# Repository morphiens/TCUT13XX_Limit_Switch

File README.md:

# TCUT13XX_Limit_Switch
Micro-limit-switch Using TCUT1300X01 Series  In this limit switch 2 Emitter are there for Redundancy , if some how on e get damage we have other one for use as backup

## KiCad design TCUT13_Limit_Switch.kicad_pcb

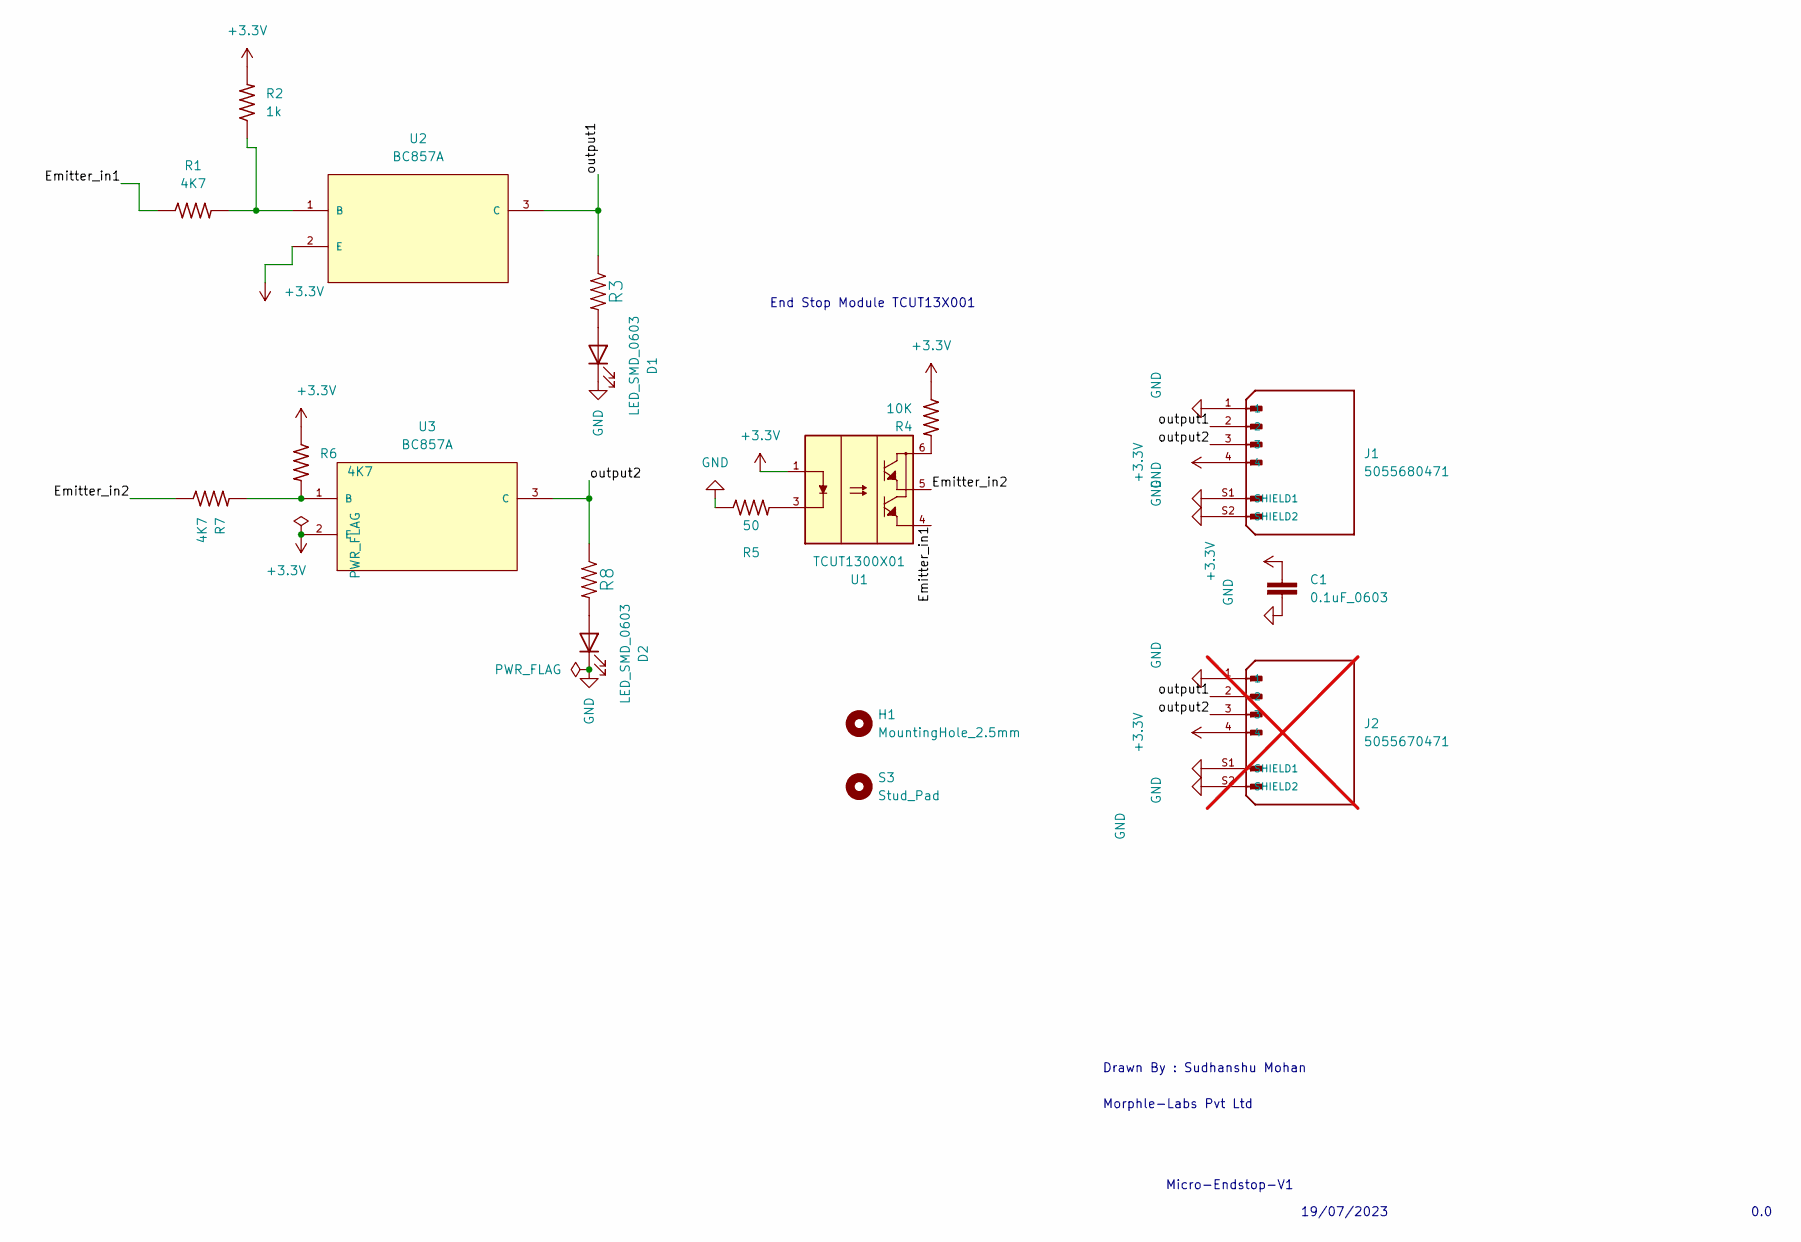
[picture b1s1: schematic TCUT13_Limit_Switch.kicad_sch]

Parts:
C1: 0.1uF_0603; Cap_0603_1608Metric
D1, D2: LED_SMD_0603; LED_0603_1608Metric; Morphle Part no. 3300042701
H1: MountingHole_2.5mm; MountingHole_2.7mm_M2.5_Pad_Via
J1: 5055680471; MOLEX_5055680471; PARTREV C
J2: 5055670471; MOLEX_5055670471; PARTREV C; not fitted
R1, R2, R5, R6, R7: 4K7_0603; R_0603_1608Metric; Morphle Part no. 3300039601
R3, R8: 1K_0603; R_0603_1608Metric; Morphle Part no. 3300039301
R4: 10K_0603; R_0603_1608Metric; Morphle Part no. 3300039401
S3: Stud_Pad; Mounting_Wuerth_WA-SMSI-M1.6_H1mm_9774010633
U1: TCUT1300X01; XDCR_TCUT1300X01; PARTREV 2.9
U2, U3: BC857A; SOT95P240X110-3N; MPN BC857A

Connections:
+3.3V: C1.1, J1.4, J2.4, R2.2, R4.1, R6.1, U1.1, U2.2 (E), U3.2 (E)
/Emitter_in1: R1.1, U1.4
/Emitter_in2: R7.1, U1.5
/output1: J1.2, J2.2, R3.1, U2.3 (C)
/output2: J1.3, J2.3, R8.1, U3.3 (C)
GND: C1.2, D1.1 (K), D2.1 (K), J1.1, J1.S1 (SHIELD1), J1.S2 (SHIELD2), J2.1, J2.S1 (SHIELD1), J2.S2 (SHIELD2), R5.1
unnamed: D1.2 (A), R3.2
unnamed: D2.2 (A), R8.2
unnamed: R4.2, U1.6
unnamed: R5.2, U1.3
unnamed: R1.2, R2.1, U2.1 (B)
unnamed: R6.2, R7.2, U3.1 (B)

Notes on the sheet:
Micro-Endstop-V1
End Stop Module TCUT13X001
19/07/2023
0.0
Morphle-Labs Pvt Ltd
Drawn By : Sudhanshu Mohan

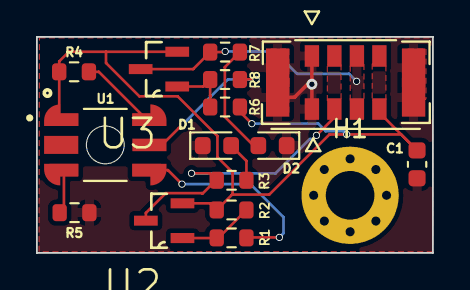
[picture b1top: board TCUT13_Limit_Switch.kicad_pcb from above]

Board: 2 copper layers, 22.0 x 12.0 mm, 18 parts (1 on the bottom side), 12 nets.

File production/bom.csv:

Designator,Footprint,Quantity,Value,LCSC Part #
C1,0603,1,0.1uF_0603,
"D1, D2",0603,2,LED_SMD_0603,
H1,MountingHole_2.7mm_M2.5_Pad_Via,1,MountingHole_2.5mm,
"Q1, Q2",BC847,2,BC847,
"R1, R2, R5, R6, R7",0603,5,4K7_0603,
"R3, R8",0603,2,1K_0603,
R4,0603,1,10K_0603,
S3,Mounting_Wuerth_WA-SMSI-M1.6_H1mm_9774010633,1,Stud_Pad,
U1,XDCR_TCUT1300X01,1,TCUT1300X01,

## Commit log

2023-07-19 Schematic and PCB file
2023-07-19 [Sudhanshu] Endstop with final Setup
2023-07-20 sudhanshu Final PCB with 2 Connector Right angle and upside Connector in a same place
2023-07-21 Final PCB Edit
2023-08-24 [sudhasnhu] added Some Change New Repo
